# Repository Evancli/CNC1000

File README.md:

# CNC1000
A parallel port to USB bridge powered by GRBL for CNC mills.

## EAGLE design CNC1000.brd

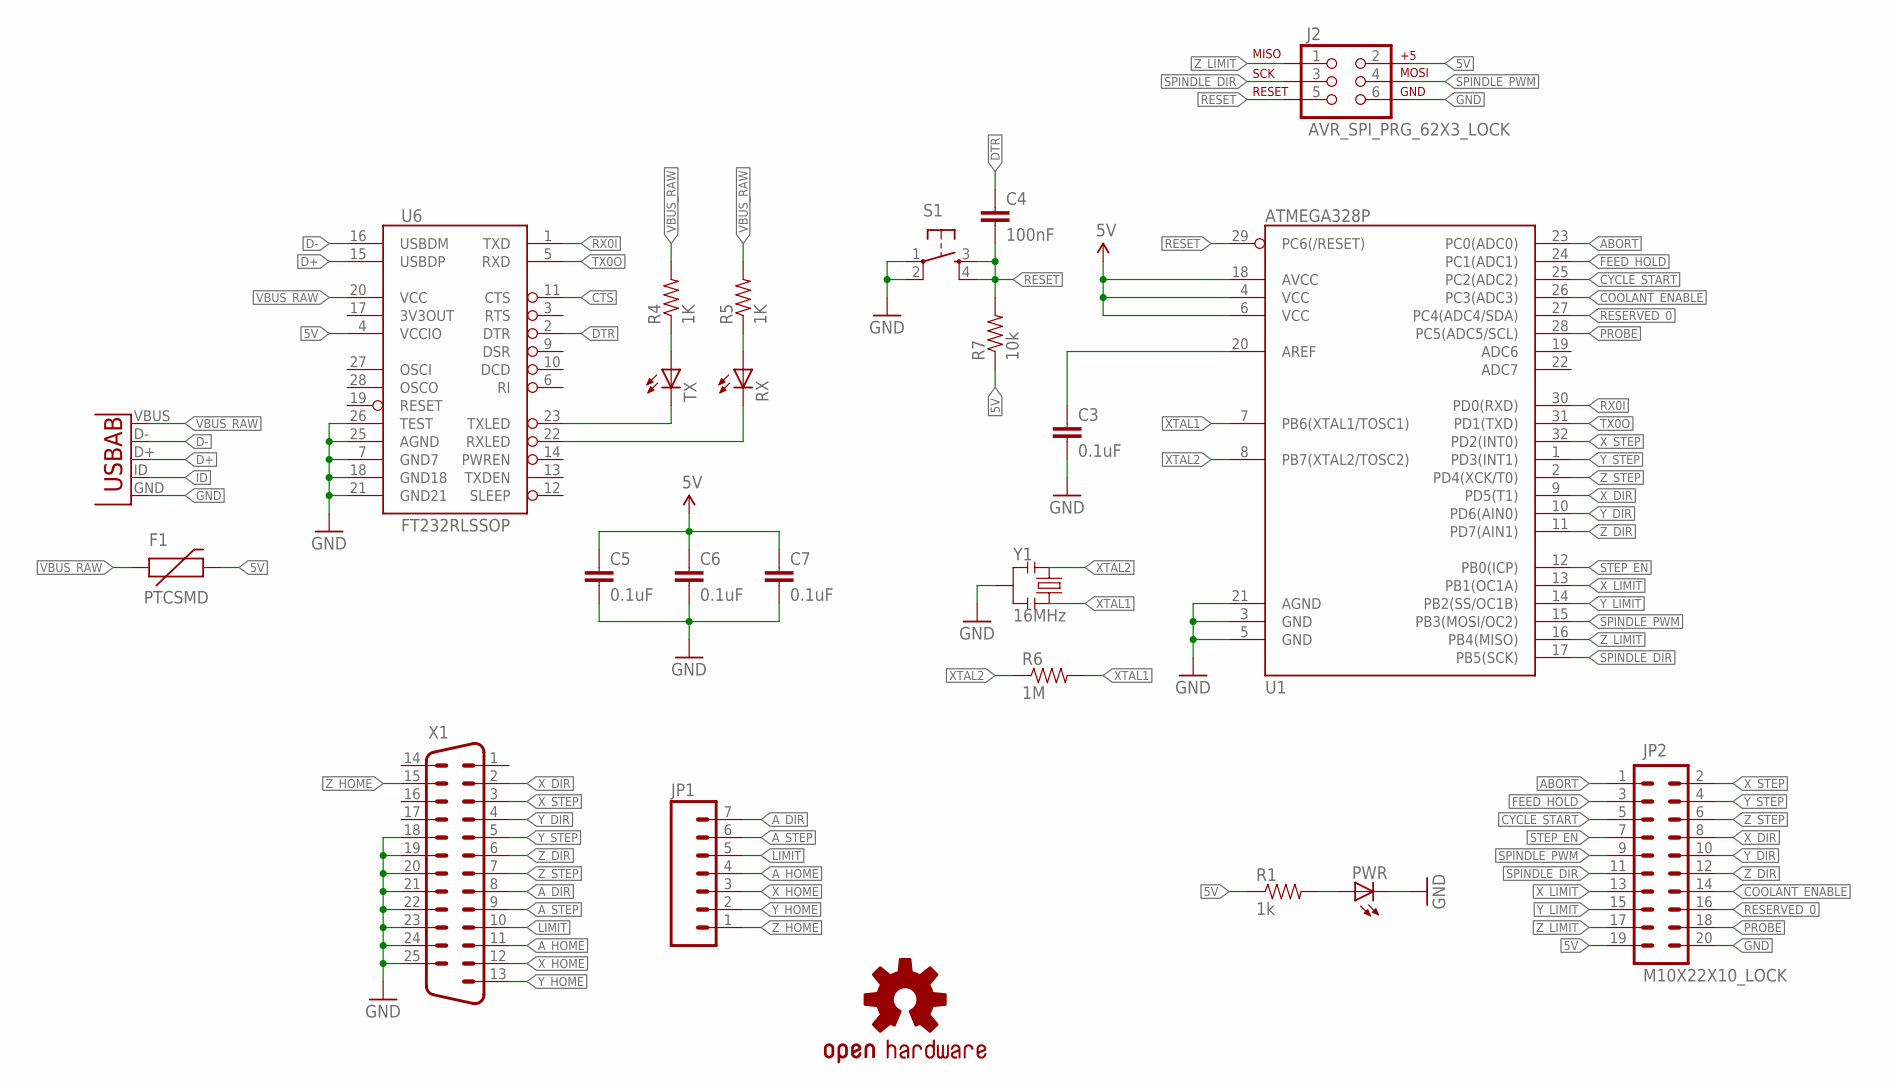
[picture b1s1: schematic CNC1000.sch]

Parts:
C3, C5, C6, C7: 0.1uF; 0805
C4: 100nF; 0805
F1: PTCSMD; PTC-1206
J2: AVR_SPI_PRG_62X3_LOCK; 2X3_LOCK
JP1: M07LOCK; 1X07_LOCK
JP2: M10X22X10_LOCK; 2X10_LOCK
LOGO2: OSHW-LOGOM; OSHW-LOGO-M
PWR: LED0603; LED-0603
R1: 1k; 0805
R4, R5: 1K; 0805
R6: 1M; 0805
R7: 10k; 0805
RX: LED0603; LED-0603
S1: TAC_SWITCHSMD; TACTILE_SWITCH_SMD
TX: LED0603; LED-0603
U1: ATMEGA328P; TQFP32-08
U4: USB-AB"; USB_AB_MICRO_1:1_V2
U6: FT232RLSSOP; SSOP28DB
X1: DB25TE; TE1734350
Y1: 16MHz; PRQC16.00SR1010V00L

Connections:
5V: C5.1, C6.1, C7.1, F1.2, J2.2, JP2.19, R1.1, R7.1, U1.4 (VCC), U1.6 (VCC), U1.18 (AVCC), U6.4 (VCCIO)
ABORT: JP2.1, U1.23 (PC0(ADC0))
A_DIR: JP1.7, X1.8
A_HOME: JP1.4, X1.11
A_STEP: JP1.6, X1.9
COOLANT_ENABLE: JP2.14, U1.26 (PC3(ADC3))
CTS: U6.11 (CTS)
CYCLE_START: JP2.5, U1.25 (PC2(ADC2))
D+: U4.D+, U6.15 (USBDP)
D-: U4.D-, U6.16 (USBDM)
DTR: C4.1, U6.2 (DTR)
FEED_HOLD: JP2.3, U1.24 (PC1(ADC1))
GND: C3.2, C5.2, C6.2, C7.2, J2.6, JP2.20, PWR.C, S1.1, S1.2, U1.3 (GND), U1.5 (GND), U1.21 (AGND), U4.GND, U6.7 (GND7), U6.18 (GND18), U6.21 (GND21), U6.25 (AGND), U6.26 (TEST), X1.18, X1.19, X1.20, X1.21, X1.22, X1.23, X1.24, X1.25, Y1.P$2 (2)
ID: U4.ID (USBID)
LIMIT: JP1.5, X1.10
unnamed: TX.C, U6.23 (TXLED)
unnamed: RX.C, U6.22 (RXLED)
unnamed: R4.1, TX.A
unnamed: R5.1, RX.A
unnamed: PWR.A, R1.2
unnamed: C3.1, U1.20 (AREF)
PROBE: JP2.18, U1.28 (PC5(ADC5/SCL))
RESERVED_0: JP2.16, U1.27 (PC4(ADC4/SDA))
RESET: C4.2, J2.5, R7.2, S1.3, S1.4, U1.29 (PC6(/RESET))
RX0I: U1.30 (PD0(RXD)), U6.1 (TXD)
SPINDLE_DIR: J2.3, JP2.11, U1.17 (PB5(SCK))
SPINDLE_PWM: J2.4, JP2.9, U1.15 (PB3(MOSI/OC2))
STEP_EN: JP2.7, U1.12 (PB0(ICP))
TX0O: U1.31 (PD1(TXD)), U6.5 (RXD)
VBUS_RAW: F1.1, R4.2, R5.2, U4.VBUS, U6.20 (VCC)
XTAL1: R6.2, U1.7 (PB6(XTAL1/TOSC1)), Y1.P$3 (3)
XTAL2: R6.1, U1.8 (PB7(XTAL2/TOSC2)), Y1.P$1 (1)
X_DIR: JP2.8, U1.9 (PD5(T1)), X1.2
X_HOME: JP1.3, X1.12
X_LIMIT: JP2.13, U1.13 (PB1(OC1A))
X_STEP: JP2.2, U1.32 (PD2(INT0)), X1.3
Y_DIR: JP2.10, U1.10 (PD6(AIN0)), X1.4
Y_HOME: JP1.2, X1.13
Y_LIMIT: JP2.15, U1.14 (PB2(SS/OC1B))
Y_STEP: JP2.4, U1.1 (PD3(INT1)), X1.5
Z_DIR: JP2.12, U1.11 (PD7(AIN1)), X1.6
Z_HOME: JP1.1, X1.15
Z_LIMIT: J2.1, JP2.17, U1.16 (PB4(MISO))
Z_STEP: JP2.6, U1.2 (PD4(XCK/T0)), X1.7

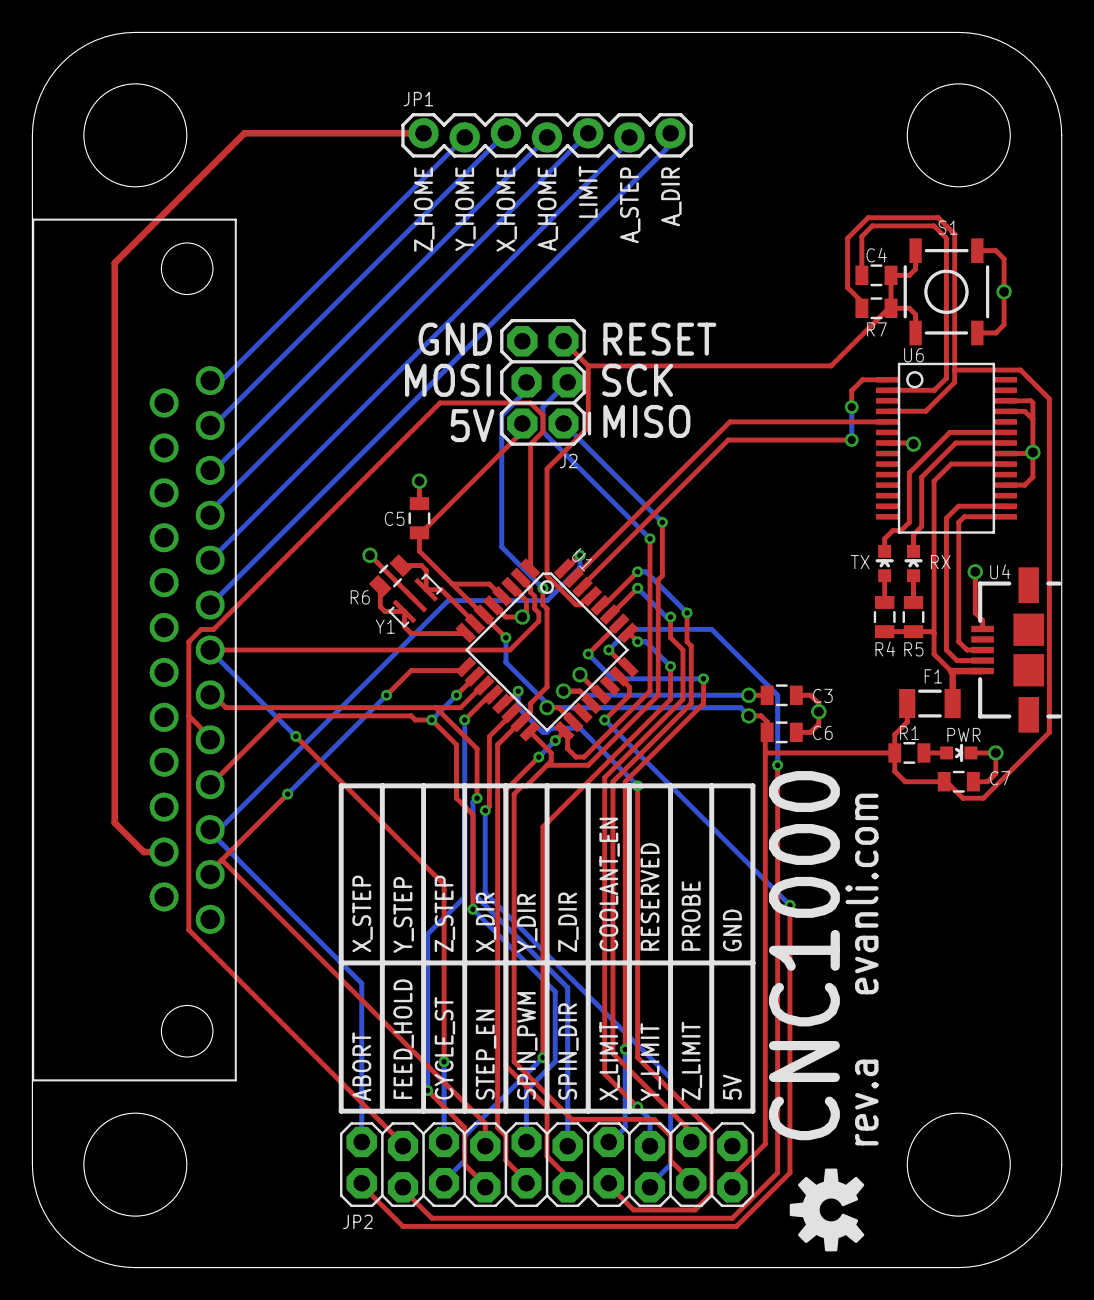
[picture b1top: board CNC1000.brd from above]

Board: 2 copper layers, 63.5 x 76.2 mm, 24 parts (0 on the bottom side), 42 nets.

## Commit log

2015-02-24 Added Eagle schematics, board and BOM files.

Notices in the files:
parts and their libraries:
SparkFun-Connectors: Licensing: Creative Commons ShareAlike 4.0 International - https://creativecommons.org/licenses/by-sa/4.0
